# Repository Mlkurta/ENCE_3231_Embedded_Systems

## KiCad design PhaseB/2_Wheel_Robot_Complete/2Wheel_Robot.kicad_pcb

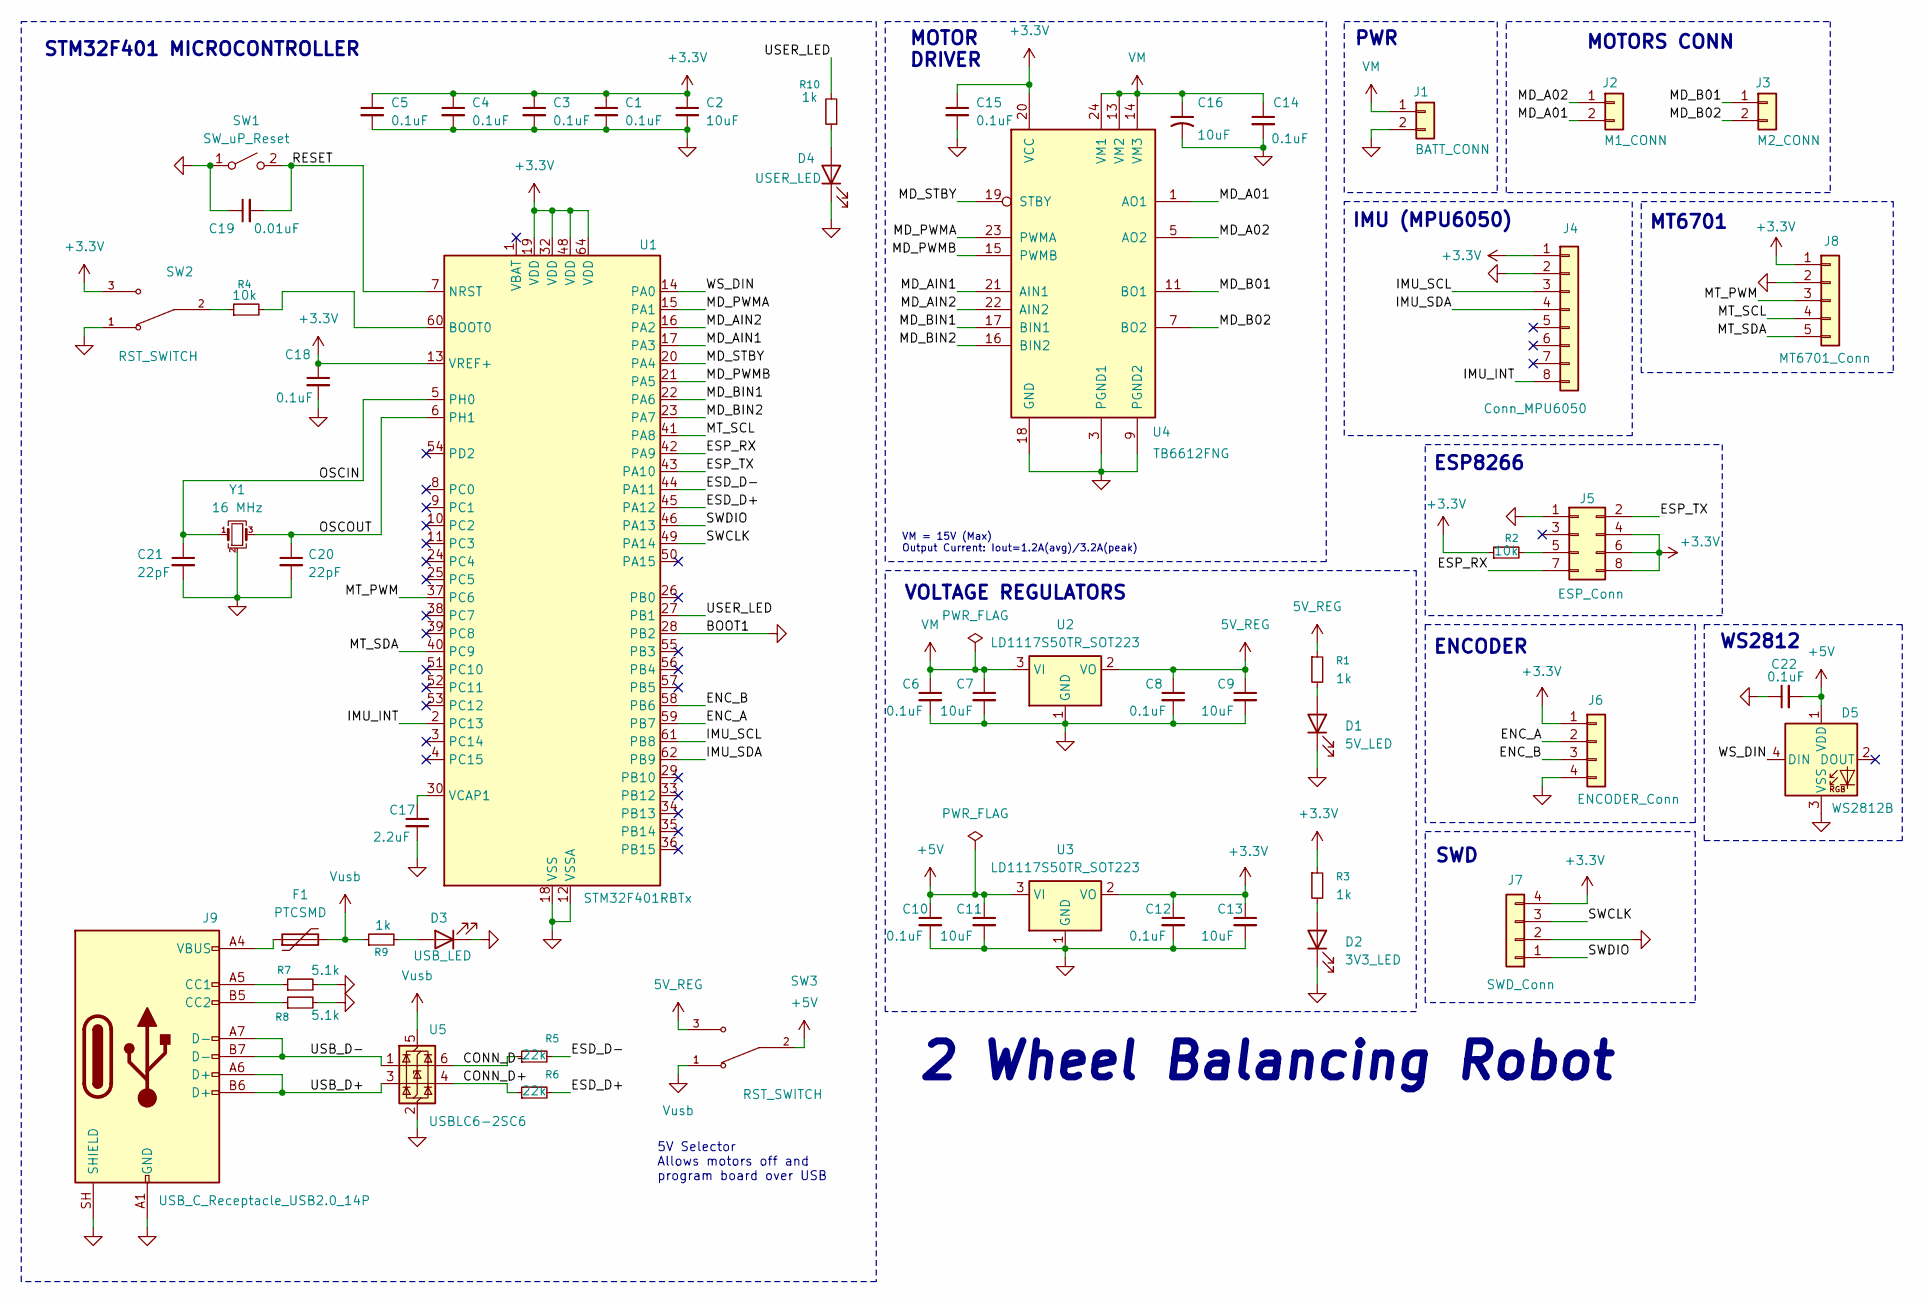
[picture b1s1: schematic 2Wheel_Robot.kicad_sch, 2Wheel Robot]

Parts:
C1, C3, C4, C5, C6, C8, C10, C12, C14, C15, C18, C22: 0.1uF; C_0805_2012Metric_Pad1.18x1.45mm_HandSolder; Mfr # KAM21BR71H104JM
C2: 10uF; C_0805_2012Metric_Pad1.18x1.45mm_HandSolder; Mfr # 810-CGA4J1X7R0J106K
C7, C9, C11, C13: 10uF; C_0805_2012Metric_Pad1.18x1.45mm_HandSolder; Mfr # KAM21BR71H104JM
C16: 10uF; CP_EIA-6032-28_Kemet-C_HandSolder
C17: 2.2uF; C_0805_2012Metric_Pad1.18x1.45mm_HandSolder; Mfr # KAM21BR71H104JM
C19: 0.01uF; C_0805_2012Metric_Pad1.18x1.45mm_HandSolder; Mfr # KAM21BR71H104JM
C20, C21: 22pF; C_0805_2012Metric_Pad1.18x1.45mm_HandSolder; Mfr # KAM21BR71H104JM
D1: 5V_LED; LED_0805_2012Metric_Pad1.15x1.40mm_HandSolder
D2: 3V3_LED; LED_0805_2012Metric_Pad1.15x1.40mm_HandSolder
D3: USB_LED; LED_0805_2012Metric_Pad1.15x1.40mm_HandSolder
D4: USER_LED; LED_0805_2012Metric_Pad1.15x1.40mm_HandSolder
D5: WS2812B; LED_WS2812B_PLCC4_5.0x5.0mm_P3.2mm
F1: PTCSMD; Fuse_1812_4532Metric
J1: BATT_CONN; JST_XH_B2B-XH-A_1x02_P2.50mm_Vertical
J2: M1_CONN; JST_XH_B2B-XH-A_1x02_P2.50mm_Vertical
J3: M2_CONN; JST_XH_B2B-XH-A_1x02_P2.50mm_Vertical
J4: Conn_MPU6050; PinSocket_1x08_P2.54mm_Vertical
J5: ESP_Conn; PinSocket_2x04_P2.54mm_Vertical
J6: ENCODER_Conn; JST_XH_B4B-XH-A_1x04_P2.50mm_Vertical
J7: SWD_Conn; PinHeader_1x04_P2.54mm_Vertical
J8: MT6701_Conn; JST_XH_B5B-XH-A_1x05_P2.50mm_Vertical
J9: USB_C_Receptacle_USB2.0_14P; USB_C_Receptacle_HCTL_HC-TYPE-C-16P-01A
R1, R3: 1k; R_0805_2012Metric_Pad1.20x1.40mm_HandSolder; Mfr # 66-WCR0805LF1001FPLT
R2, R4: 10k; R_0805_2012Metric_Pad1.20x1.40mm_HandSolder; Mfr # 603-RV0805JR-0710KL
R5, R6: 22k; R_0805_2012Metric_Pad1.20x1.40mm_HandSolder; Mfr # 603-RV0805JR-0710KL
R7, R8: 5.1k; R_0805_2012Metric_Pad1.20x1.40mm_HandSolder; Mfr # 603-RV0805JR-0710KL
R9, R10: 1k; R_0805_2012Metric_Pad1.20x1.40mm_HandSolder; Mfr # 603-RV0805JR-0710KL
SW1: SW_uP_Reset
SW2, SW3: RST_SWITCH; SW_SLW-66527511-SMT-TR; PARTREV 1.01
U1: STM32F401RBTx; LQFP-64_10x10mm_P0.5mm; MFR # STM32F401RET6
U2, U3: LD1117S50TR_SOT223; SOT-223-3_TabPin2; Mfr # 511-LD1117ASTR
U4: TB6612FNG; SSOP-24_5.3x8.2mm_P0.65mm
U5: USBLC6-2SC6; SOT-23-6
Y1: 16 MHz; Crystal_SMD_Abracon_ABM8G-4Pin_3.2x2.5mm

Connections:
5V_REG: C8.1, C9.1, R1.1, SW3.3, U2.2 (VO)
+3.3V: C1.1, C2.1, C3.1, C4.1, C5.1, C12.1, C13.1, C15.1, C18.1, J4.1, J5.4, J5.6, J5.8, J6.1, J7.4, J8.1, R2.1, R3.1, SW2.3, U1.13 (VREF+), U1.19 (VDD), U1.32 (VDD), U1.48 (VDD), U1.64 (VDD), U3.2 (VO), U4.20 (VCC)
+5V: C10.1, C11.1, C22.2, D5.1 (VDD), SW3.2, U3.3 (VI)
/CONN_D+: R6.1, U5.4 (I/O2)
/CONN_D-: R5.1, U5.6 (I/O1)
/ENC_A: J6.2, U1.59 (PB7)
/ENC_B: J6.3, U1.58 (PB6)
/ESD_D+: R6.2, U1.45 (PA12)
/ESD_D-: R5.2, U1.44 (PA11)
/ESP_RX: J5.7, U1.42 (PA9)
/ESP_TX: J5.2, U1.43 (PA10)
/IMU_INT: J4.8, U1.2 (PC13)
/IMU_SCL: J4.3, U1.61 (PB8)
/IMU_SDA: J4.4, U1.62 (PB9)
/MD_A01: J2.2, U4.1 (AO1), U4.2 (AO1)
/MD_A02: J2.1, U4.5 (AO2), U4.6 (AO2)
/MD_AIN1: U1.17 (PA3), U4.21 (AIN1)
/MD_AIN2: U1.16 (PA2), U4.22 (AIN2)
/MD_B01: J3.1, U4.11 (BO1), U4.12 (BO1)
/MD_B02: J3.2, U4.7 (BO2), U4.8 (BO2)
/MD_BIN1: U1.22 (PA6), U4.17 (BIN1)
/MD_BIN2: U1.23 (PA7), U4.16 (BIN2)
/MD_PWMA: U1.15 (PA1), U4.23 (PWMA)
/MD_PWMB: U1.21 (PA5), U4.15 (PWMB)
/MD_STBY: U1.20 (PA4), U4.19 (STBY)
/MT_PWM: J8.3, U1.37 (PC6)
/MT_SCL: J8.4, U1.41 (PA8)
/MT_SDA: J8.5, U1.40 (PC9)
/OSCIN: C21.1, U1.5 (PH0), Y1.1
/OSCOUT: C20.1, U1.6 (PH1), Y1.3
/RESET: C19.2, SW1.2 (B), U1.7 (NRST)
/SWCLK: J7.3, U1.49 (PA14)
/SWDIO: J7.1, U1.46 (PA13)
/USB_D+: J9.A6 (D+), J9.B6 (D+), U5.3 (I/O2)
/USB_D-: J9.A7 (D-), J9.B7 (D-), U5.1 (I/O1)
/USER_LED: R10.2, U1.27 (PB1)
/WS_DIN: D5.4 (DIN), U1.14 (PA0)
GND: C1.2, C2.2, C3.2, C4.2, C5.2, C6.2, C7.2, C8.2, C9.2, C10.2, C11.2, C12.2, C13.2, C14.2, C15.2, C16.2, C17.2, C18.2, C19.1, C20.2, C21.2, C22.1, D1.1 (K), D2.1 (K), D3.1 (K), D4.1 (K), D5.3 (VSS), J1.2, J4.2, J5.1, J6.4, J7.2, J8.2, J9.A1 (GND), J9.A12 (GND), J9.B1 (GND), J9.B12 (GND), J9.SH (SHIELD), R7.2, R8.2, SW1.1 (A), SW2.1, U1.12 (VSSA), U1.18 (VSS), U1.28 (PB2), U1.31 (VSS), U1.47 (VSS), U1.63 (VSS), U2.1 (GND), U3.1 (GND), U4.3 (PGND1), U4.4 (PGND1), U4.9 (PGND2), U4.10 (PGND2), U4.18 (GND), U5.2 (GND), Y1.2 (G), Y1.4 (G)
unnamed: D1.2 (A), R1.2
unnamed: D2.2 (A), R3.2
unnamed: D3.2 (A), R9.2
unnamed: D4.2 (A), R10.1
unnamed: F1.1, J9.A4 (VBUS), J9.A9 (VBUS), J9.B4 (VBUS), J9.B9 (VBUS)
unnamed: J5.5, R2.2
unnamed: J9.A5 (CC1), R7.1
unnamed: J9.B5 (CC2), R8.1
unnamed: R4.1, SW2.2
unnamed: R4.2, U1.60 (BOOT0)
unnamed: C17.1, U1.30 (VCAP1)
VM: C6.1, C7.1, C14.1, C16.1, J1.1, U2.3 (VI), U4.13 (VM2), U4.14 (VM3), U4.24 (VM1)
Vusb: F1.2, R9.1, SW3.1, U5.5 (VBUS)

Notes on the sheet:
2 Wheel Balancing Robot
IMU (MPU6050)
SWD
PWR
WS2812
STM32F401 MICROCONTROLLER
MOTOR DRIVER
MOTORS CONN
VOLTAGE REGULATORS
ESP8266
MT6701
VM = 15V (Max) Output Current: Iout=1.2A(avg)/3.2A(peak)
ENCODER
5V Selector Allows motors off and program board over USB

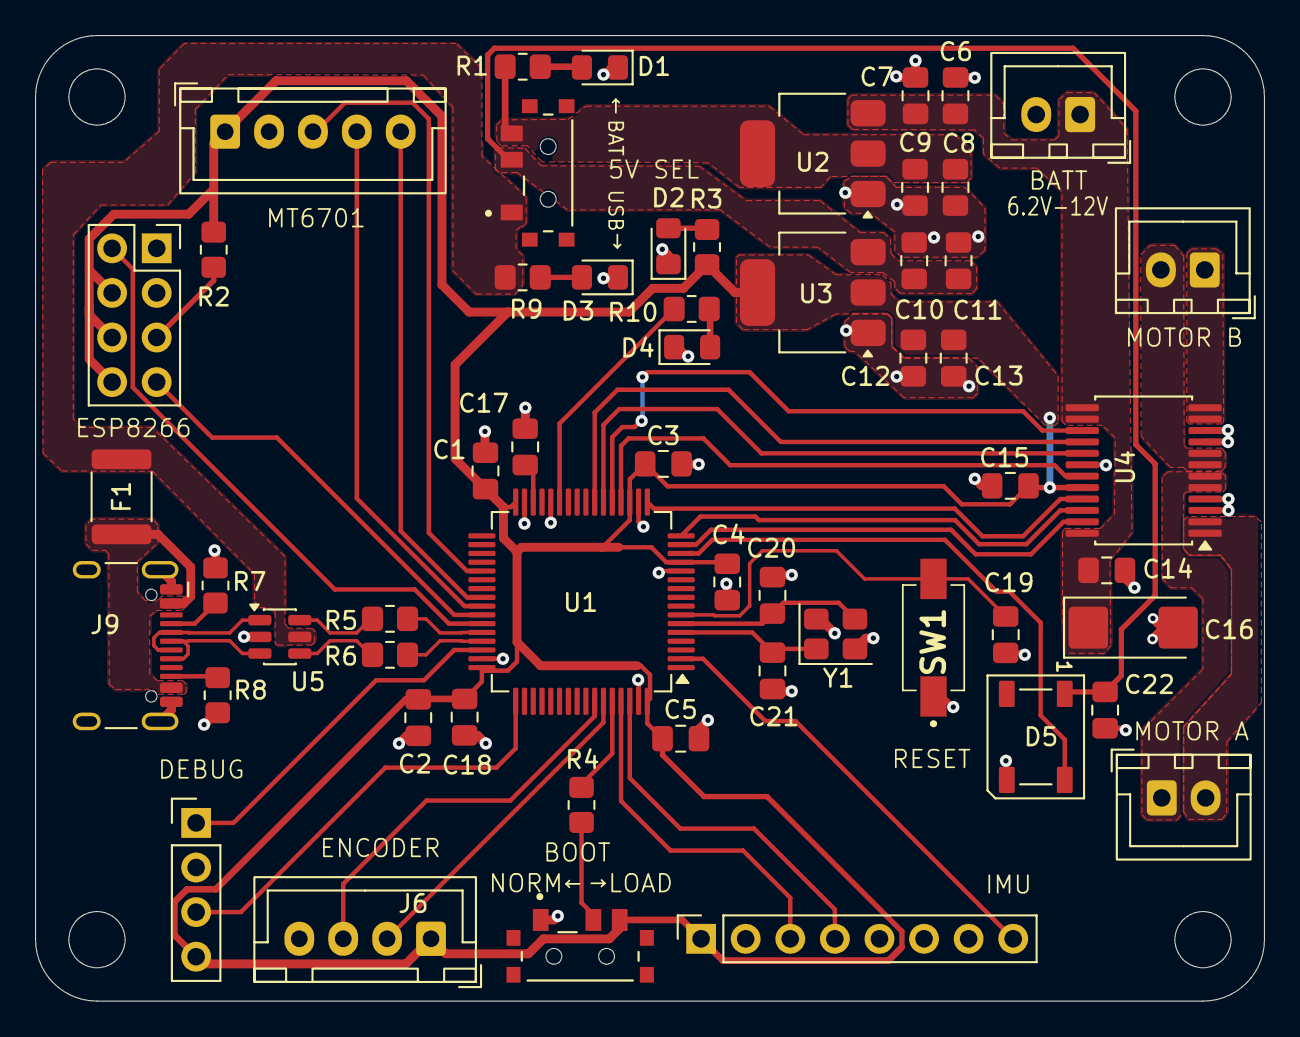
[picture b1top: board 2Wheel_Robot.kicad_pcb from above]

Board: 2 copper layers, 70.0 x 55.0 mm, 60 parts (0 on the bottom side), 51 nets.

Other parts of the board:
H1, H2, H3, H4: MountingHole; MountingHole_3.2mm_M3

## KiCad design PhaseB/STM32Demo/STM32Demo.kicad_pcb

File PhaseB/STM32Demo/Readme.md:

# STM32 Demo

This is a Project created by mirroring the KiCAD board design process by Philip Salmony of Phil's Lab.

The creation video can be found here: https://youtu.be/aVUqaB0IMh4?si=m5vGeWEMC6P6GTJ3

Schematic:

Board layout:

Board Model:

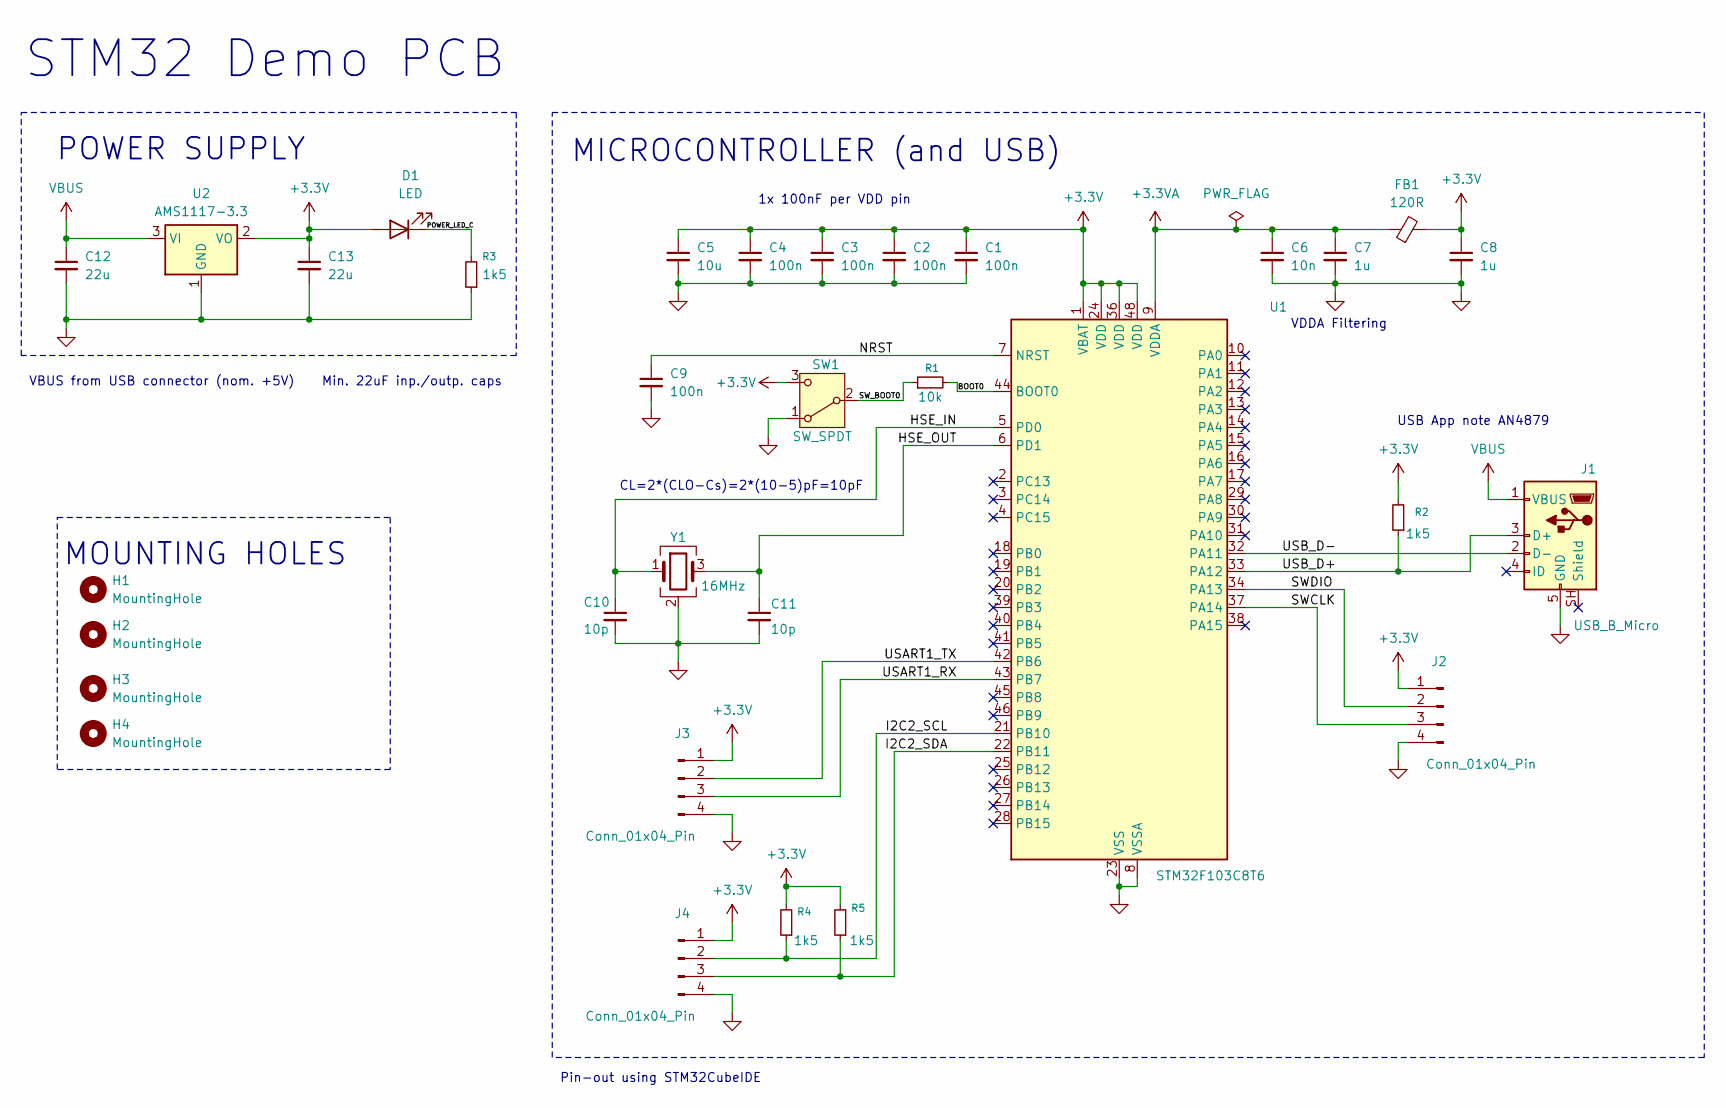
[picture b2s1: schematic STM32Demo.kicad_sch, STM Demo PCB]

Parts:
C1, C2, C3, C4: 100n; C_0402_1005Metric
C5: 10u; C_0603_1608Metric
C6: 10n; C_0402_1005Metric
C7, C8: 1u; C_0603_1608Metric
C9: 100n; C_0603_1608Metric
C10, C11: 10p; C_0402_1005Metric
C12, C13: 22u; C_0805_2012Metric
D1: LED; LED_0603_1608Metric
FB1: 120R; L_0603_1608Metric
H1, H2, H3, H4: MountingHole; MountingHole_2.1mm
J1: USB_B_Micro; USB_Micro-B_Wuerth_629105150521
J2, J3, J4: Conn_01x04_Pin; PinHeader_1x04_P2.54mm_Vertical
R1: 10k; R_0402_1005Metric
R2, R3, R4, R5: 1k5; R_0402_1005Metric
SW1: SW_SPDT; SW_SPDT_PCM12
U1: STM32F103C8T6; LQFP-48_7x7mm_P0.5mm
U2: AMS1117-3.3; SOT-223-3_TabPin2
Y1: 16MHz; Crystal_SMD_3225-4Pin_3.2x2.5mm

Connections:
+3.3V: C1.1, C2.1, C3.1, C4.1, C5.1, C8.1, C13.1, D1.2 (A), FB1.2, J2.1, J3.1, J4.1, R2.2, R4.2, R5.2, SW1.3 (C), U1.1 (VBAT), U1.24 (VDD), U1.36 (VDD), U1.48 (VDD), U2.2 (VO)
+3.3VA: C6.1, C7.1, FB1.1, U1.9 (VDDA)
/BOOT0: R1.2, U1.44 (BOOT0)
/HSE_IN: C10.1, U1.5 (PD0), Y1.1
/HSE_OUT: C11.1, U1.6 (PD1), Y1.3
/I2C2_SCL: J4.2, R4.1, U1.21 (PB10)
/I2C2_SDA: J4.3, R5.1, U1.22 (PB11)
/NRST: C9.1, U1.7 (NRST)
/POWER_LED_C: D1.1 (K), R3.2
/SWCLK: J2.3, U1.37 (PA14)
/SWDIO: J2.2, U1.34 (PA13)
/SW_BOOT0: R1.1, SW1.2 (B)
/USART1_RX: J3.3, U1.43 (PB7)
/USART1_TX: J3.2, U1.42 (PB6)
/USB_D+: J1.3 (D+), R2.1, U1.33 (PA12)
/USB_D-: J1.2 (D-), U1.32 (PA11)
GND: C1.2, C2.2, C3.2, C4.2, C5.2, C6.2, C7.2, C8.2, C9.2, C10.2, C11.2, C12.2, C13.2, J1.5 (GND), J2.4, J3.4, J4.4, R3.1, SW1.1 (A), U1.8 (VSSA), U1.23 (VSS), U1.35 (VSS), U1.47 (VSS), U2.1 (GND), Y1.2 (G), Y1.4 (G)
VBUS: C12.1, J1.1 (VBUS), U2.3 (VI)

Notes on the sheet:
Pin-out using STM32CubeIDE
1x 100nF per VDD pin
STM32 Demo PCB
CL=2*(CLO-Cs)=2*(10-5)pF=10pF
VBUS from USB connector (nom. +5V) Min. 22uF inp./outp. caps
VDDA Filtering
MOUNTING HOLES
POWER SUPPLY
MICROCONTROLLER (and USB)
USB App note AN4879

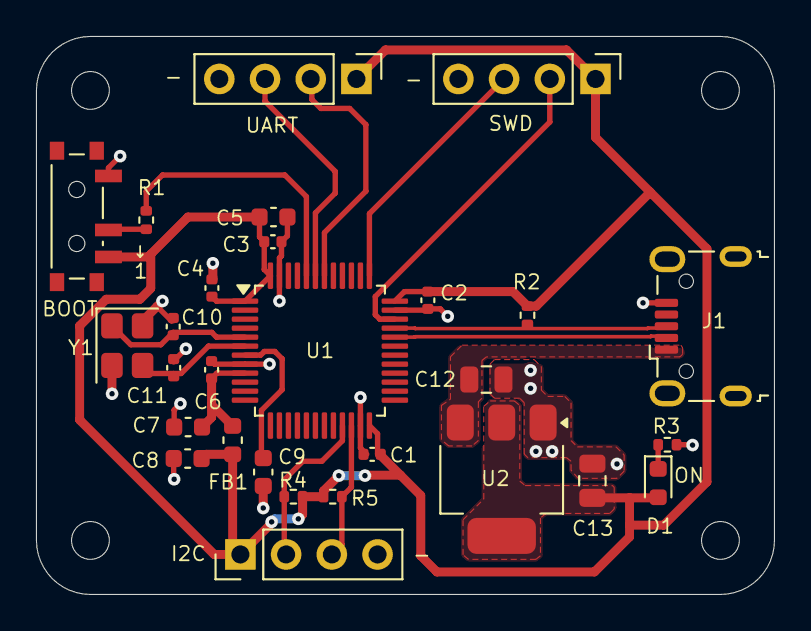
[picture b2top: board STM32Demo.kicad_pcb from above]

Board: 2 copper layers, 41.0 x 31.0 mm, 32 parts (0 on the bottom side), 18 nets.

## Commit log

2026-06-10 Add files via upload
    Adding files that previously didn't upload
2026-06-10 Add files via upload
    Added files which originally failed in upload
2026-06-10 Add files via upload
    Zip file with entire contents of the project folder for 2 wheel balancing
